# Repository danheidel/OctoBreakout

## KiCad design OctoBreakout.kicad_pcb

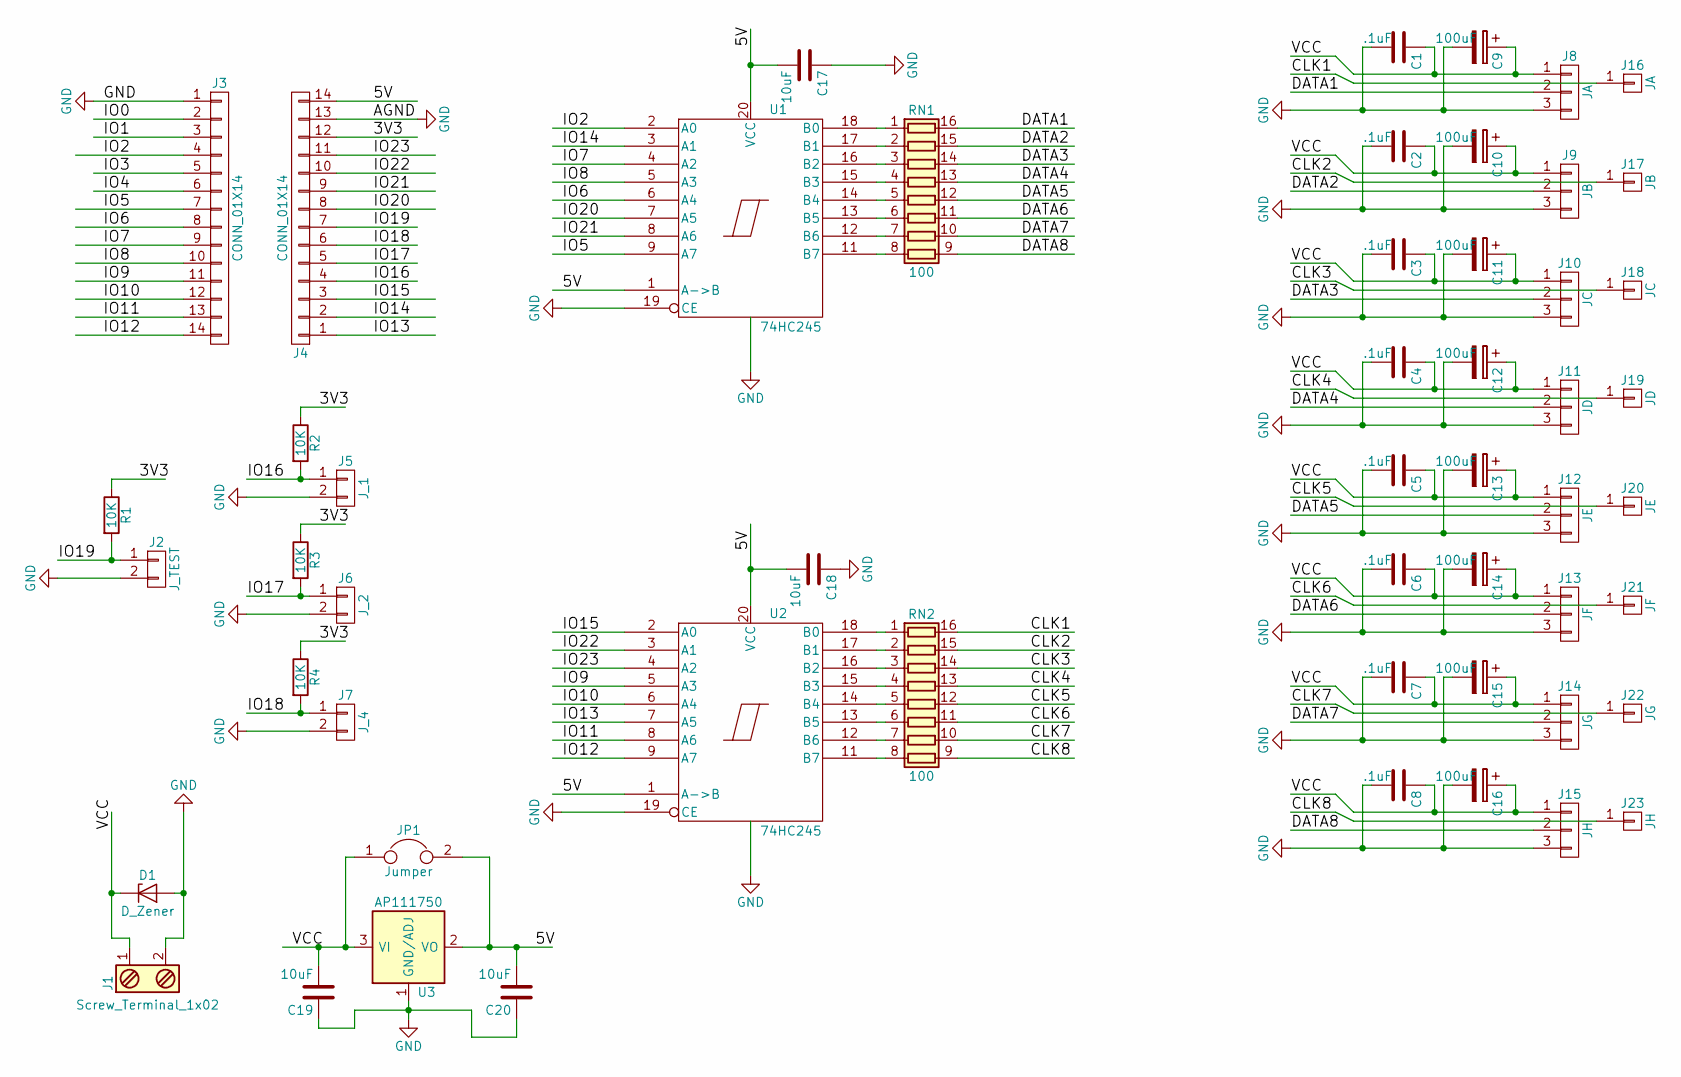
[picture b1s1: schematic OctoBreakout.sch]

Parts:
C1, C2, C3, C4, C5, C6, C7, C8: .1uF; C_0805
C9, C10, C11, C12, C13, C14, C15, C16: 100uF; CP_Radial_D5.0mm_P2.00mm
C17, C18, C19, C20: 10uF; C_1206
D1: D_Zener; D_SOD-123
J1: Screw_Terminal_1x02; WAGO_2POS_7.5MM_TERM_BLOCK
J2: J_TEST; Pin_Header_Straight_1x02_Pitch2.54mm
J3, J4: CONN_01X14; Pin_Header_Straight_1x14_Pitch2.54mm
J5: J_1; Pin_Header_Straight_1x02_Pitch2.54mm
J6: J_2; Pin_Header_Straight_1x02_Pitch2.54mm
J7: J_4; Pin_Header_Straight_1x02_Pitch2.54mm
J8: JA; Pin_Header_Straight_1x03_Pitch2.54mm
J9: JB; Pin_Header_Straight_1x03_Pitch2.54mm
J10: JC; Pin_Header_Straight_1x03_Pitch2.54mm
J11: JD; Pin_Header_Straight_1x03_Pitch2.54mm
J12: JE; Pin_Header_Straight_1x03_Pitch2.54mm
J13: JF; Pin_Header_Straight_1x03_Pitch2.54mm
J14: JG; Pin_Header_Straight_1x03_Pitch2.54mm
J15: JH; Pin_Header_Straight_1x03_Pitch2.54mm
J16: JA; Pin_Header_Straight_1x01_Pitch2.54mm
J17: JB; Pin_Header_Straight_1x01_Pitch2.54mm
J18: JC; Pin_Header_Straight_1x01_Pitch2.54mm
J19: JD; Pin_Header_Straight_1x01_Pitch2.54mm
J20: JE; Pin_Header_Straight_1x01_Pitch2.54mm
J21: JF; Pin_Header_Straight_1x01_Pitch2.54mm
J22: JG; Pin_Header_Straight_1x01_Pitch2.54mm
J23: JH; Pin_Header_Straight_1x01_Pitch2.54mm
JP1: Jumper
R1, R2, R3, R4: 10K; R_0805
RN1, RN2: 100; R_Array_Convex_8x0602
U1, U2: 74HC245; TSSOP-20_4.4x6.5mm_Pitch0.65mm
U3: AP111750; SOT-223

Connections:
/3V3: J4.12, R1.1, R2.1, R3.1, R4.1
/5V: C17.2, C18.2, C20.2, J4.14, JP1.2, U1.1 (A->B), U1.20 (VCC), U2.1 (A->B), U2.20 (VCC), U3.2 (VO), U3.4 (VO)
/CLK1: J16.1, RN2.16 (R1.2)
/CLK2: J17.1, RN2.15 (R2.2)
/CLK3: J18.1, RN2.14 (R3.2)
/CLK4: J19.1, RN2.13 (R4.2)
/CLK5: J20.1, RN2.12 (R5.2)
/CLK6: J21.1, RN2.11 (R6.2)
/CLK7: J22.1, RN2.10 (R7.2)
/CLK8: J23.1, RN2.9 (R8.2)
/DATA1: J8.2, RN1.16 (R1.2)
/DATA2: J9.2, RN1.15 (R2.2)
/DATA3: J10.2, RN1.14 (R3.2)
/DATA4: J11.2, RN1.13 (R4.2)
/DATA5: J12.2, RN1.12 (R5.2)
/DATA6: J13.2, RN1.11 (R6.2)
/DATA7: J14.2, RN1.10 (R7.2)
/DATA8: J15.2, RN1.9 (R8.2)
/IO0: J3.2
/IO1: J3.3
/IO2: J3.4, U1.2 (A0)
/IO3: J3.5
/IO4: J3.6
/IO5: J3.7, U1.9 (A7)
/IO6: J3.8, U1.6 (A4)
/IO7: J3.9, U1.4 (A2)
/IO8: J3.10, U1.5 (A3)
/IO9: J3.11, U2.5 (A3)
/IO10: J3.12, U2.6 (A4)
/IO11: J3.13, U2.8 (A6)
/IO12: J3.14, U2.9 (A7)
/IO13: J4.1, U2.7 (A5)
/IO14: J4.2, U1.3 (A1)
/IO15: J4.3, U2.2 (A0)
/IO16: J4.4, J5.1, R2.2
/IO17: J4.5, J6.1, R3.2
/IO18: J4.6, J7.1, R4.2
/IO19: J2.1, J4.7, R1.2
/IO20: J4.8, U1.7 (A5)
/IO21: J4.9, U1.8 (A6)
/IO22: J4.10, U2.3 (A1)
/IO23: J4.11, U2.4 (A2)
/VCC: C1.1, C2.1, C3.1, C4.1, C5.1, C6.1, C7.1, C8.1, C9.1, C10.1, C11.1, C12.1, C13.1, C14.1, C15.1, C16.1, C19.2, D1.1 (K), J1.1, J8.1, J9.1, J10.1, J11.1, J12.1, J13.1, J14.1, J15.1, JP1.1, U3.3 (VI)
GND: C1.2, C2.2, C3.2, C4.2, C5.2, C6.2, C7.2, C8.2, C9.2, C10.2, C11.2, C12.2, C13.2, C14.2, C15.2, C16.2, C17.1, C18.1, C19.1, C20.1, D1.2 (A), J1.2, J2.2, J3.1, J4.13, J5.2, J6.2, J7.2, J8.3, J9.3, J10.3, J11.3, J12.3, J13.3, J14.3, J15.3, U1.10 (GND), U1.19 (CE), U2.10 (GND), U2.19 (CE), U3.1 (GND/ADJ)
unnamed: RN1.1 (R1.1), U1.18 (B0)
unnamed: RN1.2 (R2.1), U1.17 (B1)
unnamed: RN1.3 (R3.1), U1.16 (B2)
unnamed: RN1.4 (R4.1), U1.15 (B3)
unnamed: RN1.5 (R5.1), U1.14 (B4)
unnamed: RN1.6 (R6.1), U1.13 (B5)
unnamed: RN1.7 (R7.1), U1.12 (B6)
unnamed: RN1.8 (R8.1), U1.11 (B7)
unnamed: RN2.1 (R1.1), U2.18 (B0)
unnamed: RN2.2 (R2.1), U2.17 (B1)
unnamed: RN2.3 (R3.1), U2.16 (B2)
unnamed: RN2.4 (R4.1), U2.15 (B3)
unnamed: RN2.5 (R5.1), U2.14 (B4)
unnamed: RN2.6 (R6.1), U2.13 (B5)
unnamed: RN2.7 (R7.1), U2.12 (B6)
unnamed: RN2.8 (R8.1), U2.11 (B7)

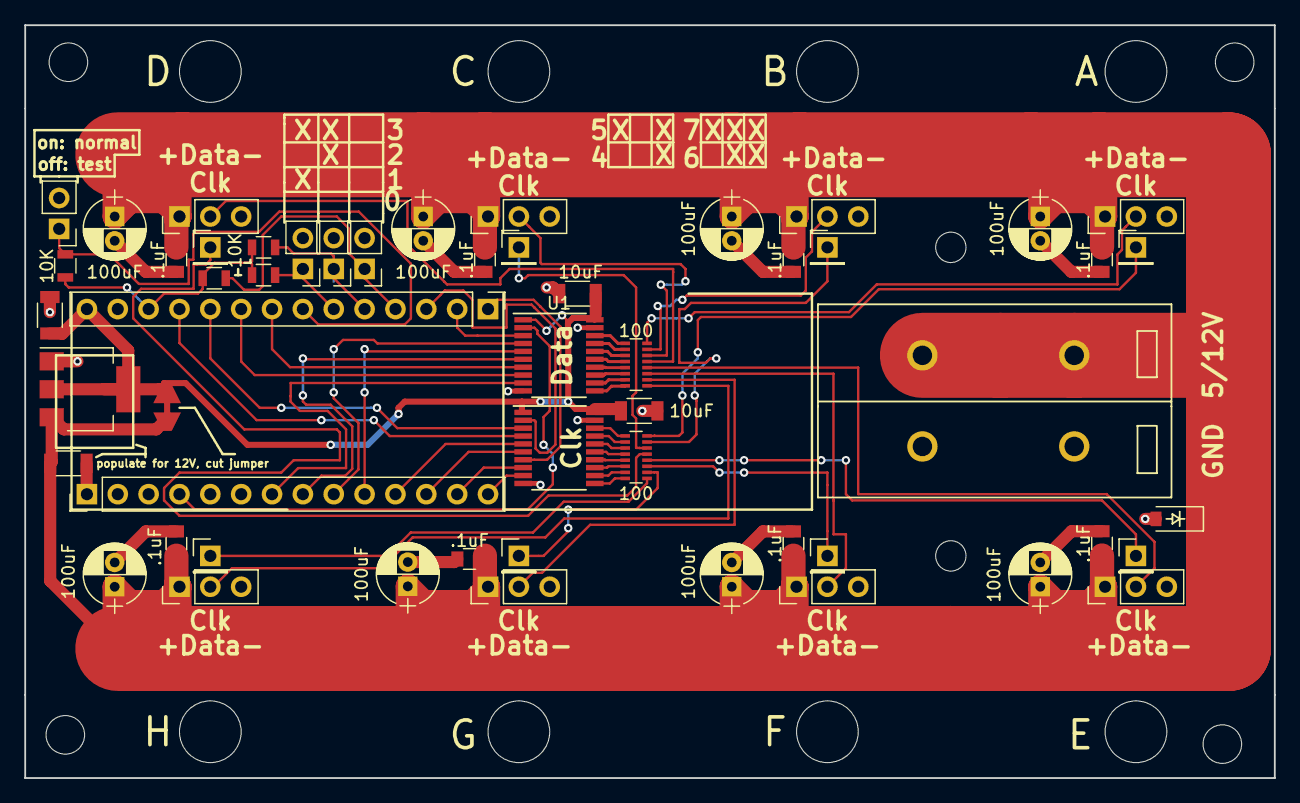
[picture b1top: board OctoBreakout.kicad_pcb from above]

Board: 2 copper layers, 102.9 x 62.0 mm, 54 parts (0 on the bottom side), 56 nets.

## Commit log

2017-04-15 monir revisions
